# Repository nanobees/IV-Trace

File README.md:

# IV-Trace
DIY Four Probe IV Characterization for Graphene Studies

Eagle and LabView files for DIY four probe mesaurement device for graphene hall effect devices and transistor.

The files in this repository are for graphene device characterization project for Advanced Project Laboratory course that held 
in  Physics Department of Istanbul Technical University, Istanbul with the facilities of Nanoscale Surface Science Laboratory
with the Supervisor of Prof. Oguzhan Gurlu. The project is suported by Tubitak 1003 project with the grant number of 114F036.

In this project an Arduino is used for measuring currents and a Tektronix made oscillator is for reading voltage across a four probe graphene device. The voltage is supplied via Keithley 2400 sourcemeter. The Sourcemeter is controlled via LabView with specific instrument drivers. Oscilloscope and Arduino Data read via Labview with specific instrument driver for 
oscilloscope and LINX drivers for Arduino. In Labview the Current-Voltage graphs plotted for four separate probes.

In order to read the current flowing through the sample and I/V converter is made with precise shunt resistors. After that
the voltage converted flows through a very precise instrumentation amplifier; Analog Devices AD629 amplifier. The signal than
goes through Arduino and via serial port read with LabView.

For further information you can contact with me; haltugyildirim_at_protonmail.com

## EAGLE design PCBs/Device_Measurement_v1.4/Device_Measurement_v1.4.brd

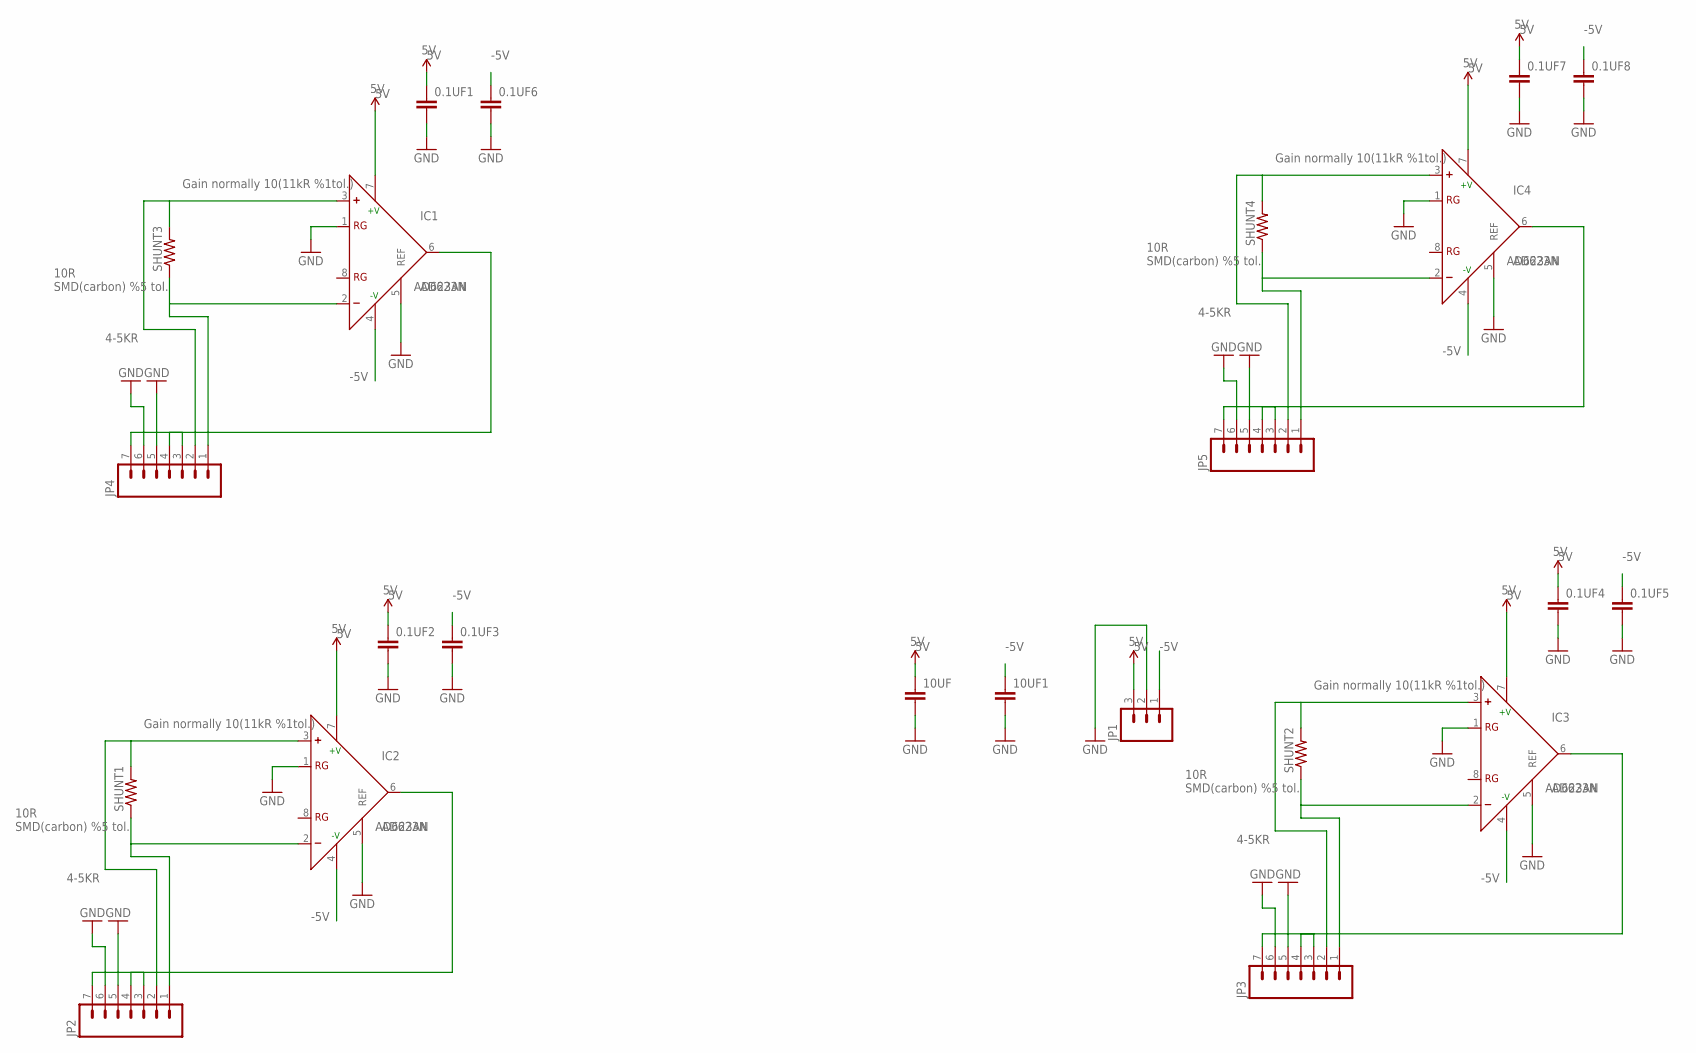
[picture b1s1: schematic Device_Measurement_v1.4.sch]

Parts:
0.1UF1, 0.1UF2, 0.1UF3, 0.1UF4, 0.1UF5, 0.1UF6, 0.1UF7, 0.1UF8, 10UF, 10UF1: CAPPTH1; CAP-PTH-5MM
IC1, IC2, IC3, IC4: AD623N; DIL08
JP1: M03LOCK; 1X03_LOCK
JP2, JP3, JP4, JP5: M07; 1X07
SHUNT1, SHUNT2, SHUNT3, SHUNT4: RESISTOR1206; 1206

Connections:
5V: 0.1UF1.1, 0.1UF2.1, 0.1UF4.1, 0.1UF7.1, 10UF.1, IC1.7 (+V), IC2.7 (+V), IC3.7 (+V), IC4.7 (+V), JP1.3
-5V: 0.1UF3.1, 0.1UF5.1, 0.1UF6.1, 0.1UF8.1, 10UF1.1, IC1.4 (-V), IC2.4 (-V), IC3.4 (-V), IC4.4 (-V), JP1.1
GND: 0.1UF1.2, 0.1UF2.2, 0.1UF3.2, 0.1UF4.2, 0.1UF5.2, 0.1UF6.2, 0.1UF7.2, 0.1UF8.2, 10UF.2, 10UF1.2, IC1.1 (RG), IC1.5 (REF), IC2.1 (RG), IC2.5 (REF), IC3.1 (RG), IC3.5 (REF), IC4.1 (RG), IC4.5 (REF), JP1.2, JP2.5, JP2.6, JP3.5, JP3.6, JP4.5, JP4.6, JP5.5, JP5.6
unnamed: IC2.3 (+), JP2.2, SHUNT1.2
unnamed: IC2.2 (-), JP2.1, SHUNT1.1
unnamed: IC1.3 (+), JP4.2, SHUNT3.2
unnamed: IC1.2 (-), JP4.1, SHUNT3.1
unnamed: IC1.6 (OUT), JP4.7
unnamed: JP4.3, JP4.4
unnamed: IC3.3 (+), JP3.2, SHUNT2.2
unnamed: IC2.6 (OUT), JP2.7
unnamed: JP2.3, JP2.4
unnamed: IC3.2 (-), JP3.1, SHUNT2.1
unnamed: IC3.6 (OUT), JP3.7
unnamed: JP3.3, JP3.4
unnamed: IC4.3 (+), JP5.2, SHUNT4.2
unnamed: IC4.2 (-), JP5.1, SHUNT4.1
unnamed: IC4.6 (OUT), JP5.7
unnamed: JP5.3, JP5.4

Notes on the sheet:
10R SMD(carbon) %5 tol.
Gain normally 10(11kR %1tol.)
4-5KR
AD623AN

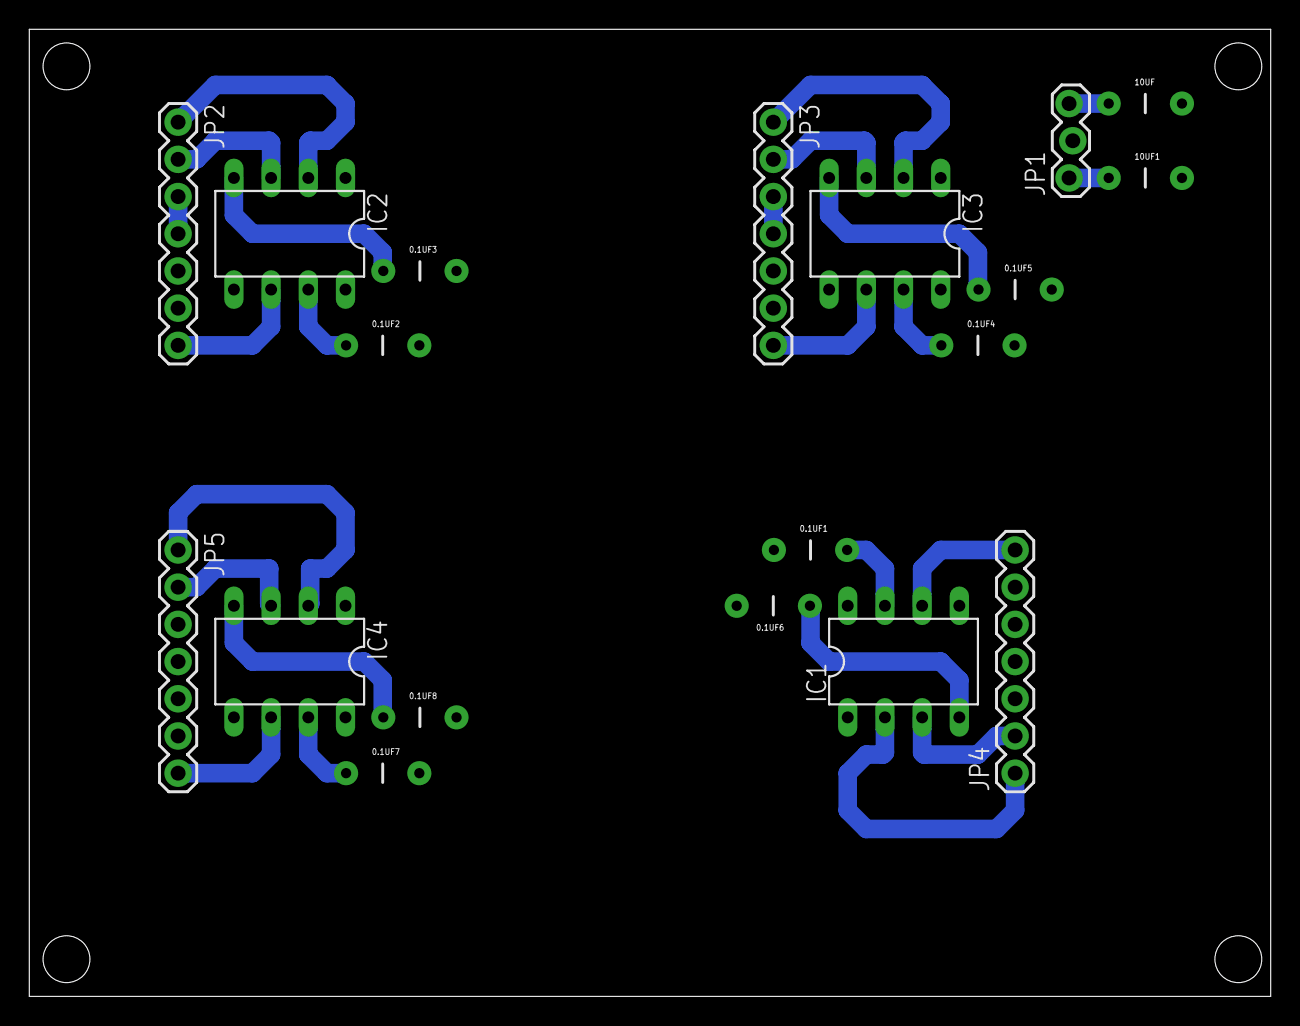
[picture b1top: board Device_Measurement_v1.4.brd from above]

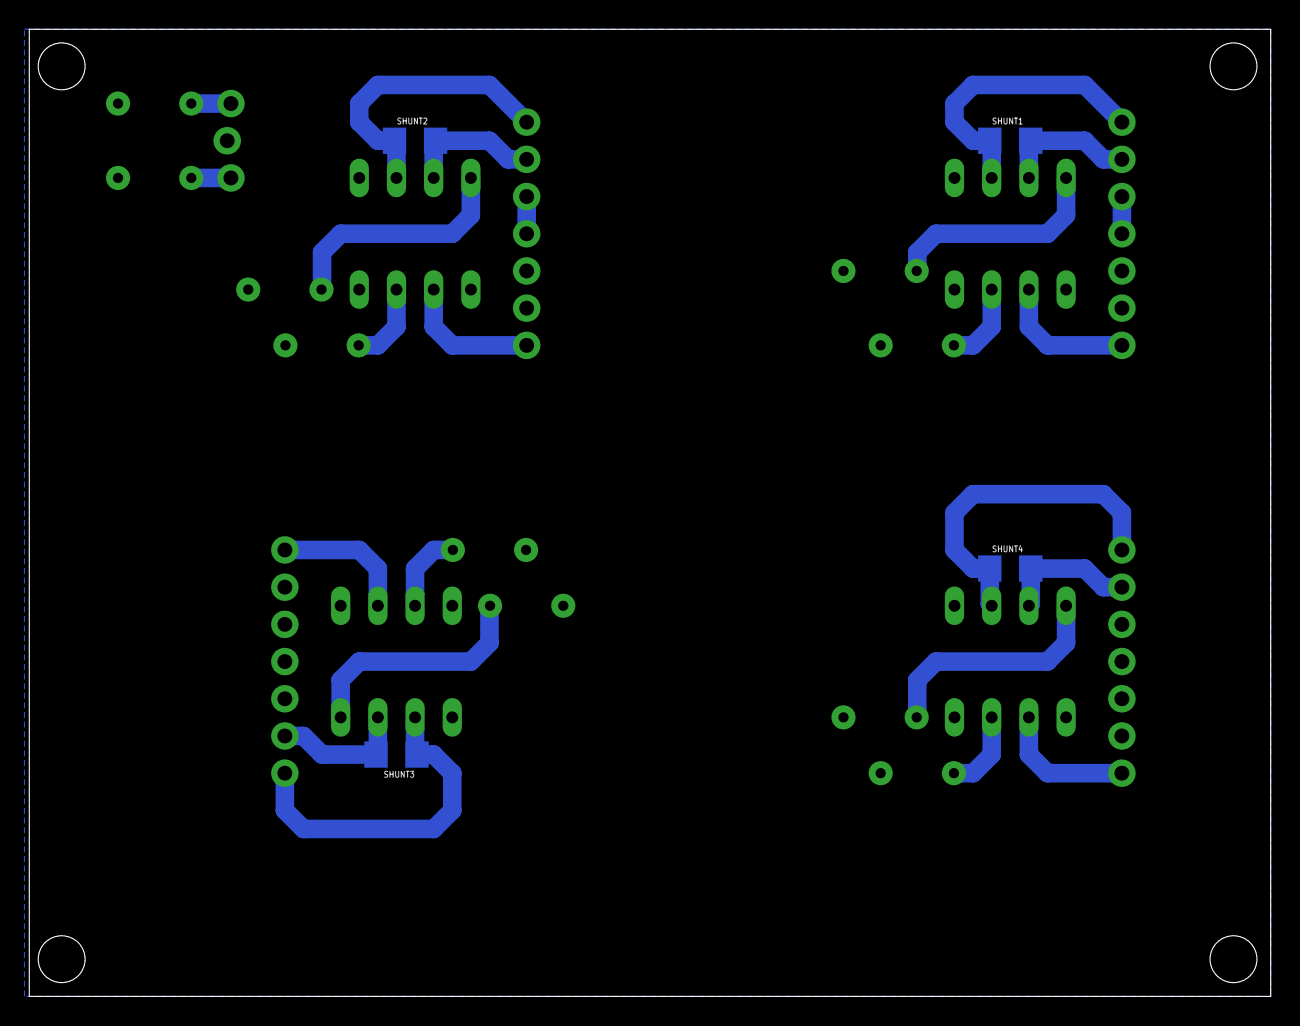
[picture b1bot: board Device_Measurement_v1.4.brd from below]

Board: 2 copper layers, 84.8 x 66.0 mm, 23 parts (4 on the bottom side), 19 nets.

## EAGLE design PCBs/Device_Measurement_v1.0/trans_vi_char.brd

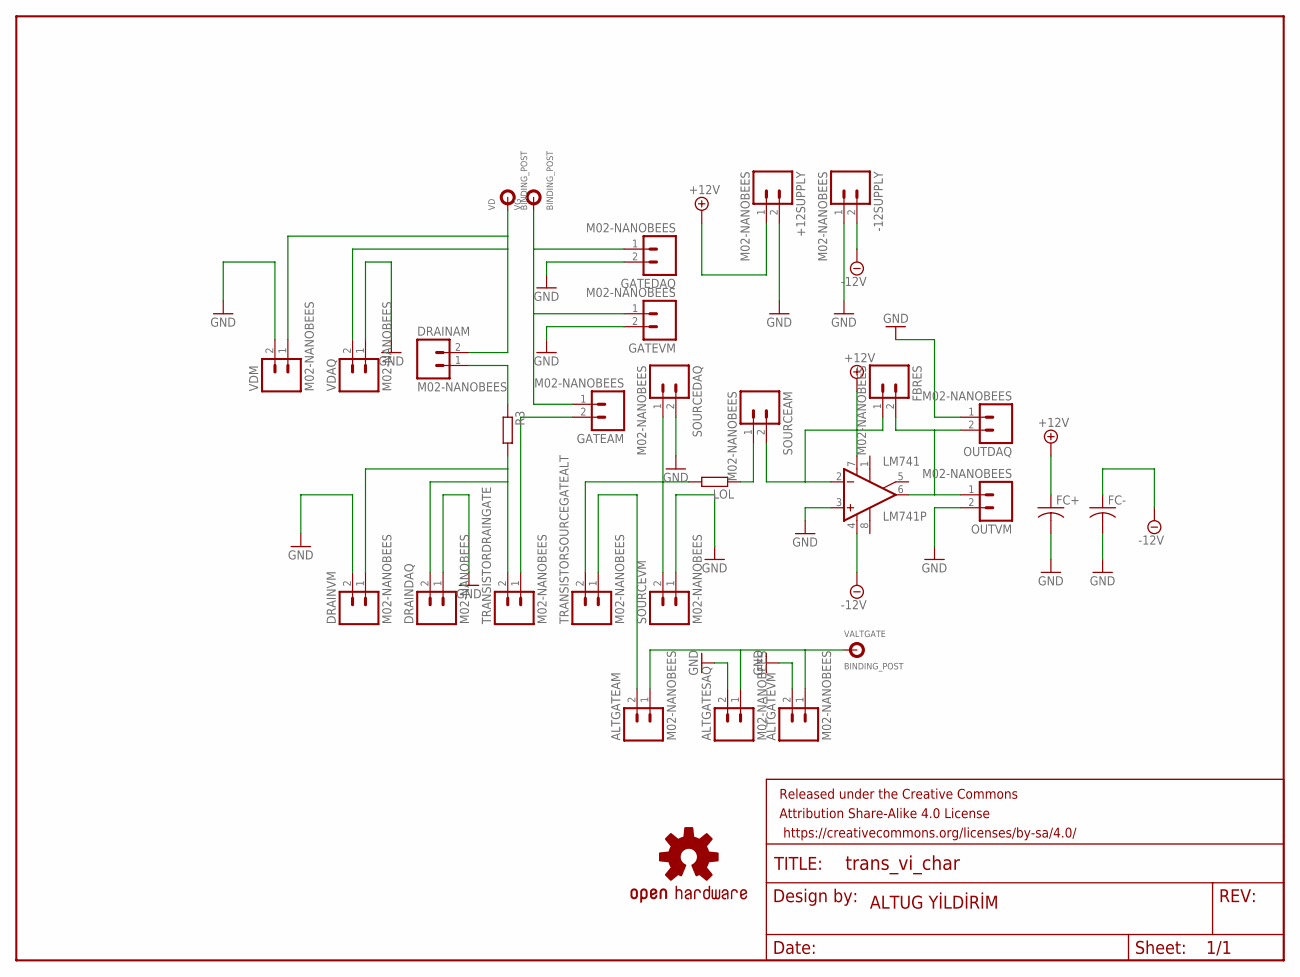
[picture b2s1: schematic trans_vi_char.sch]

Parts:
+12SUPPLY: M02-NANOBEES
-12SUPPLY: M02-NANOBEES
ALTGATEAM: M02-NANOBEES
ALTGATESAQ: M02-NANOBEES
ALTGATEVM: M02-NANOBEES
DRAINAM: M02-NANOBEES
DRAINDAQ: M02-NANOBEES
DRAINVM: M02-NANOBEES
FBRES: M02-NANOBEES
FC+: C-US025-025X050; C025-025X050
FC-: C-US025-025X050; C025-025X050
FRAME1: FRAME-LETTER; CREATIVE_COMMONS
GATEAM: M02-NANOBEES
GATEDAQ: M02-NANOBEES
GATEVM: M02-NANOBEES
LM741: LM741P; DIL08
LOGO1: OSHW-LOGOM; OSHW-LOGO-M
LOL: R-EU_0204/7; 0204/7
OUTDAQ: M02-NANOBEES
OUTVM: M02-NANOBEES
R3: R-EU_0204/7; 0204/7
SOURCEAM: M02-NANOBEES
SOURCEDAQ: M02-NANOBEES
SOURCEVM: M02-NANOBEES
TRANSISTORDRAINGATE: M02-NANOBEES
TRANSISTORSOURCEGATEALT: M02-NANOBEES
VALTGATE: BINDING_POST
VD: BINDING_POST
VDAQ: M02-NANOBEES
VDM: M02-NANOBEES
VG: BINDING_POST

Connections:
+12V: +12SUPPLY.1, FC+.1, LM741.7 (V+)
-12V: -12SUPPLY.2, FC-.1, LM741.4 (V-)
GND: +12SUPPLY.2, -12SUPPLY.1, ALTGATESAQ.2, ALTGATEVM.2, DRAINDAQ.1, DRAINVM.2, FC+.2, FC-.2, GATEDAQ.2, GATEVM.2, LM741.3 (-IN), OUTDAQ.1, OUTVM.2, SOURCEDAQ.2, SOURCEVM.1, VDAQ.1, VDM.2
unnamed: FBRES.2, LM741.6 (OUT), OUTDAQ.2, OUTVM.1
unnamed: FBRES.1, LM741.2 (+IN), SOURCEAM.2
unnamed: DRAINDAQ.2, DRAINVM.1, R3.2, TRANSISTORDRAINGATE.2
unnamed: LOL.2, SOURCEDAQ.1, SOURCEVM.2, TRANSISTORSOURCEGATEALT.2
unnamed: DRAINAM.1, R3.1
unnamed: ALTGATEAM.2, TRANSISTORSOURCEGATEALT.1
unnamed: GATEAM.2, TRANSISTORDRAINGATE.1
unnamed: GATEAM.1, GATEDAQ.1, GATEVM.1, VG.P$1
unnamed: DRAINAM.2, VD.P$1, VDAQ.2, VDM.1
unnamed: ALTGATEAM.1, ALTGATESAQ.1, ALTGATEVM.1, VALTGATE.P$1
unnamed: LOL.1, SOURCEAM.1

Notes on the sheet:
ALTUG YİLDİRİM

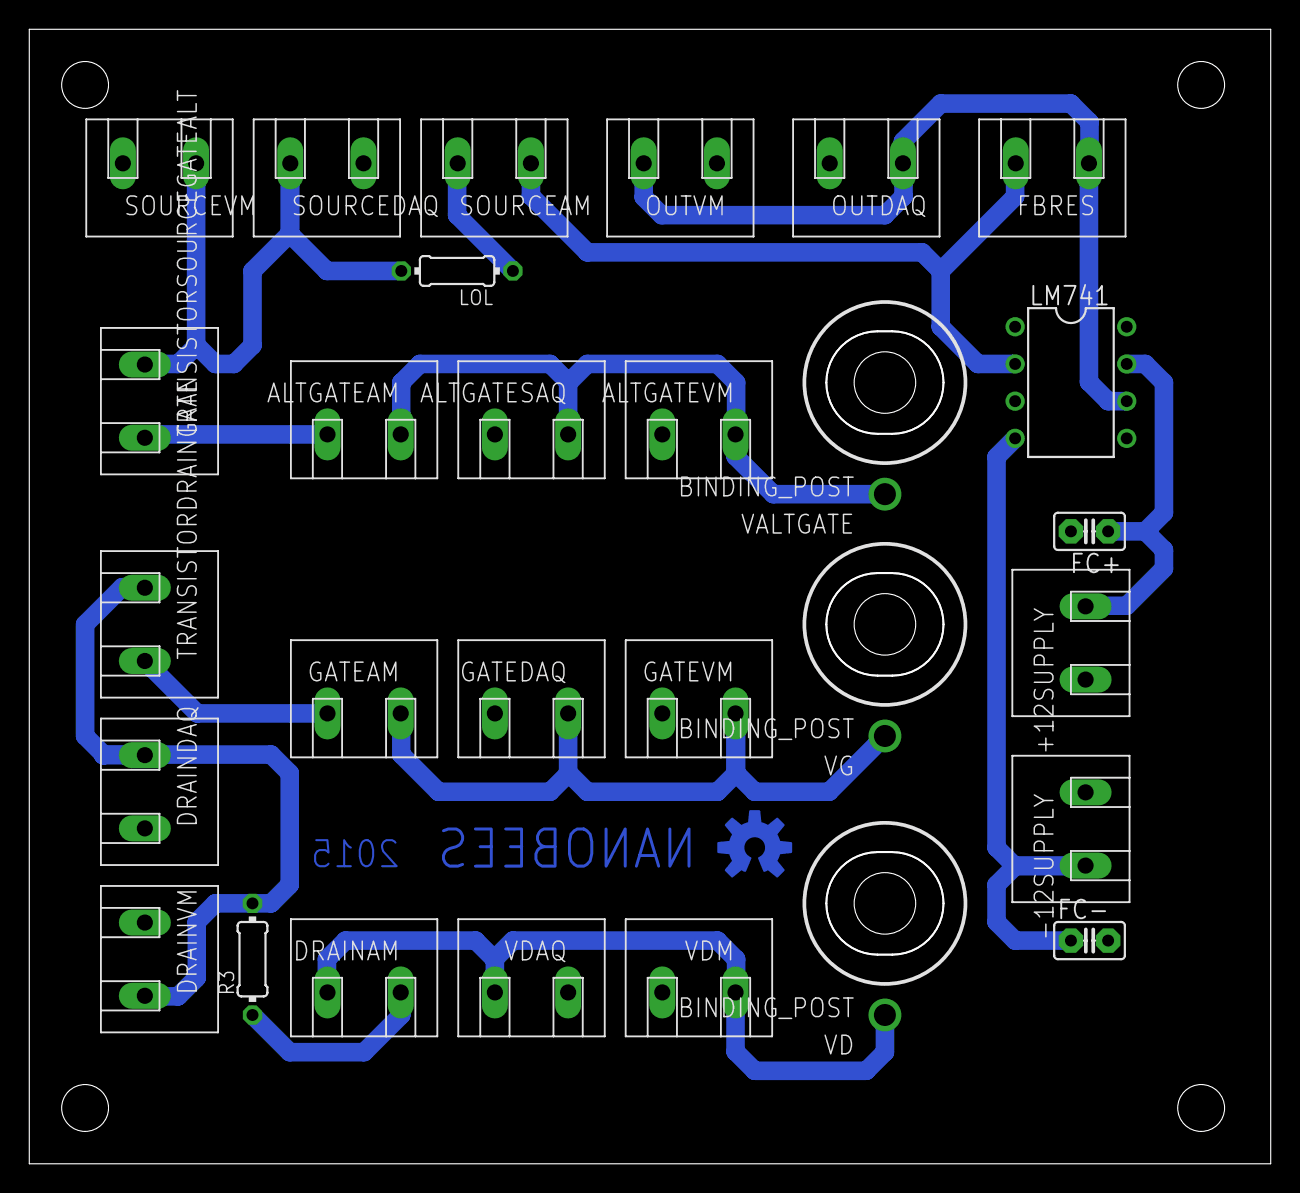
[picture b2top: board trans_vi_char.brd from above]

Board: 2 copper layers, 84.6 x 77.3 mm, 31 parts (0 on the bottom side), 14 nets.

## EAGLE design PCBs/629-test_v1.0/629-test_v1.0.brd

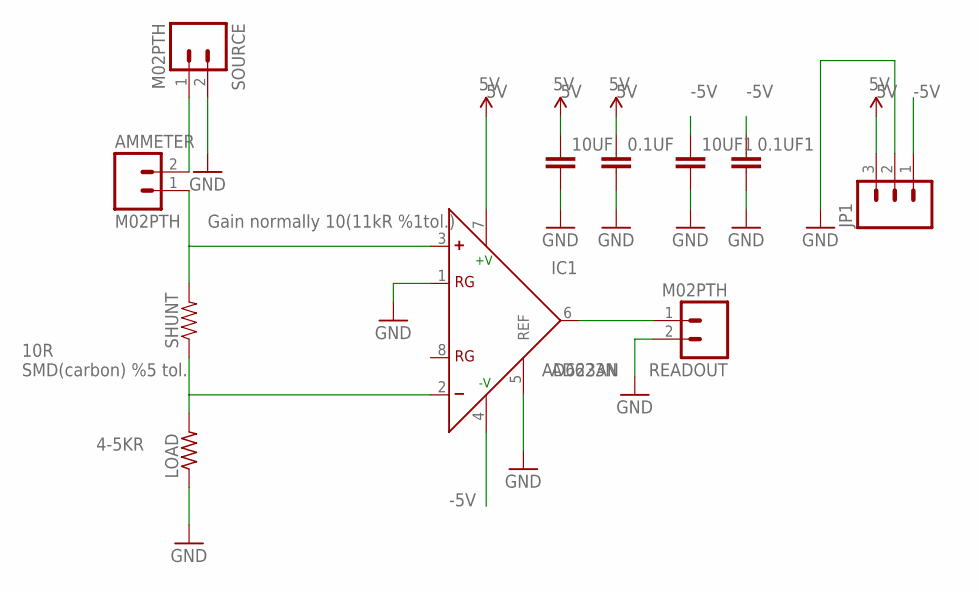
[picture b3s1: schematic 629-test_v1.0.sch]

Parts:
0.1UF, 0.1UF1, 10UF, 10UF1: CAPPTH1; CAP-PTH-5MM
AMMETER: M02PTH; 1X02
IC1: AD623N; DIL08
JP1: M03LOCK; 1X03_LOCK
LOAD: R-US_0207/10; 0207/10
READOUT: M02PTH; 1X02
SHUNT: RESISTOR1206; 1206
SOURCE: M02PTH; 1X02

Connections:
5V: 0.1UF.1, 10UF.1, IC1.7 (+V), JP1.3
-5V: 0.1UF1.1, 10UF1.1, IC1.4 (-V), JP1.1
GND: 0.1UF.2, 0.1UF1.2, 10UF.2, 10UF1.2, IC1.1 (RG), IC1.5 (REF), JP1.2, LOAD.1, READOUT.2, SOURCE.2
unnamed: AMMETER.1, IC1.3 (+), SHUNT.2
unnamed: IC1.2 (-), LOAD.2, SHUNT.1
unnamed: AMMETER.2, SOURCE.1
unnamed: IC1.6 (OUT), READOUT.1

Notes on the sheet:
10R SMD(carbon) %5 tol.
Gain normally 10(11kR %1tol.)
4-5KR
AD623AN

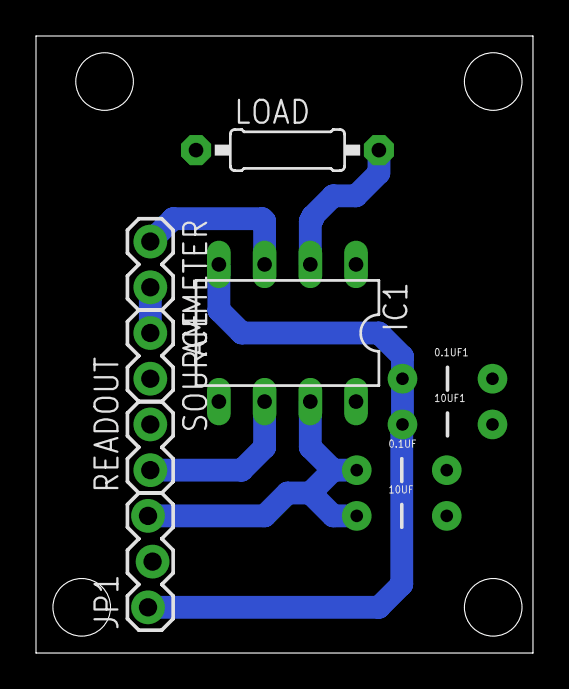
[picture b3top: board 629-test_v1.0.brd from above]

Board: 2 copper layers, 27.6 x 34.3 mm, 11 parts (1 on the bottom side), 7 nets.

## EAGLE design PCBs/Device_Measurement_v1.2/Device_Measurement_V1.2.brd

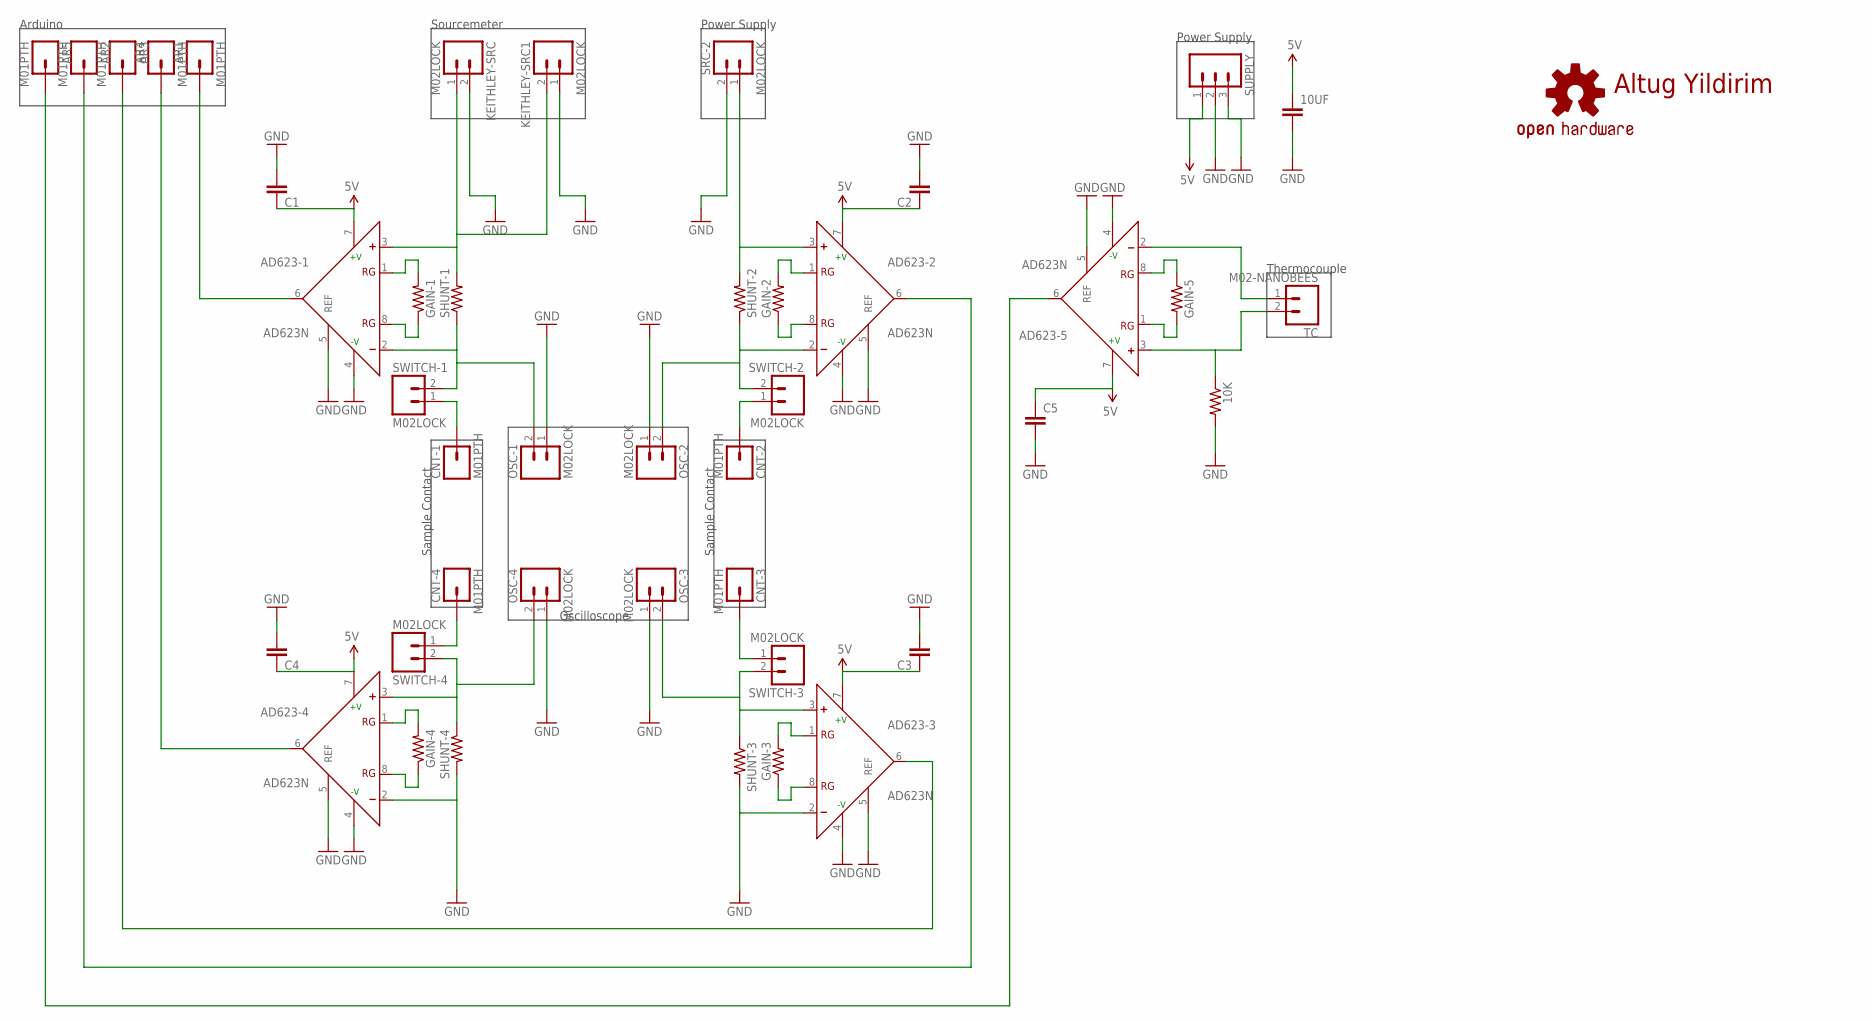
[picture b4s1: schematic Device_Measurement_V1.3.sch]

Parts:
10K: R-US_0207/10; 0207/10
10UF: CAPPTH1; CAP-PTH-5MM
AD623-1, AD623-2, AD623-3, AD623-4, AD623-5: AD623N; DIL08
AR1, AR2, AR3, AR4, AR5: M01PTH; 1X01
C1, C2, C3, C4, C5: CAPPTH1; CAP-PTH-5MM
CNT-1, CNT-2, CNT-3, CNT-4: M01PTH; 1X01
GAIN-1, GAIN-2, GAIN-3, GAIN-4, GAIN-5: R-US_0207/10; 0207/10
KEITHLEY-SRC, KEITHLEY-SRC1: M02LOCK; 1X02_LOCK
LOGO1: OSHW-LOGOM; OSHW-LOGO-M
OSC-1, OSC-2, OSC-3, OSC-4: M02LOCK; 1X02_LOCK
SHUNT-1, SHUNT-2, SHUNT-3, SHUNT-4: RESISTOR1206; 1206
SRC-2: M02LOCK; 1X02_LOCK
SUPPLY: M03PTH; 1X03
SWITCH-1, SWITCH-2, SWITCH-3, SWITCH-4: M02LOCK; 1X02_LOCK
TC: M02-NANOBEES

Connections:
5V: 10UF.1, AD623-1.7 (+V), AD623-2.7 (+V), AD623-3.7 (+V), AD623-4.7 (+V), AD623-5.7 (+V), C1.1, C2.1, C3.1, C4.1, C5.1, SUPPLY.1
GND: 10K.2, 10UF.2, AD623-1.4 (-V), AD623-1.5 (REF), AD623-2.4 (-V), AD623-2.5 (REF), AD623-3.2 (-), AD623-3.4 (-V), AD623-3.5 (REF), AD623-4.2 (-), AD623-4.4 (-V), AD623-4.5 (REF), AD623-5.4 (-V), AD623-5.5 (REF), C1.2, C2.2, C3.2, C4.2, C5.2, KEITHLEY-SRC.2, KEITHLEY-SRC1.1, OSC-1.1, OSC-2.1, OSC-3.1, OSC-4.1, SHUNT-3.2, SHUNT-4.2, SRC-2.2, SUPPLY.2, SUPPLY.3
unnamed: AD623-1.6 (OUT), AR1.1
unnamed: CNT-1.1, SWITCH-1.1
unnamed: AD623-2.6 (OUT), AR2.1
unnamed: AD623-1.1 (RG), GAIN-1.2
unnamed: AD623-4.6 (OUT), AR4.1
unnamed: AD623-1.8 (RG), GAIN-1.1
unnamed: AD623-3.6 (OUT), AR3.1
unnamed: AD623-2.2 (-), OSC-2.2, SHUNT-2.1, SWITCH-2.2
unnamed: AD623-5.6 (OUT), AR5.1
unnamed: AD623-4.3 (+), OSC-4.2, SHUNT-4.1, SWITCH-4.2
unnamed: AD623-2.3 (+), SHUNT-2.2, SRC-2.1
unnamed: CNT-2.1, SWITCH-2.1
unnamed: AD623-2.1 (RG), GAIN-2.2
unnamed: AD623-2.8 (RG), GAIN-2.1
unnamed: AD623-3.3 (+), OSC-3.2, SHUNT-3.1, SWITCH-3.2
unnamed: 10K.1, AD623-5.3 (+), TC.2
unnamed: CNT-4.1, SWITCH-4.1
unnamed: CNT-3.1, SWITCH-3.1
unnamed: AD623-3.1 (RG), GAIN-3.2
unnamed: AD623-3.8 (RG), GAIN-3.1
unnamed: AD623-4.1 (RG), GAIN-4.2
unnamed: AD623-4.8 (RG), GAIN-4.1
unnamed: AD623-5.2 (-), TC.1
unnamed: AD623-5.1 (RG), GAIN-5.2
unnamed: AD623-5.8 (RG), GAIN-5.1
unnamed: AD623-1.2 (-), OSC-1.2, SHUNT-1.1, SWITCH-1.2
unnamed: AD623-1.3 (+), KEITHLEY-SRC.1, KEITHLEY-SRC1.2, SHUNT-1.2

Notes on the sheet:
Altug Yildirim
Oscilloscope
Sample Contact
Sourcemeter
Power Supply
Arduino
Thermocouple

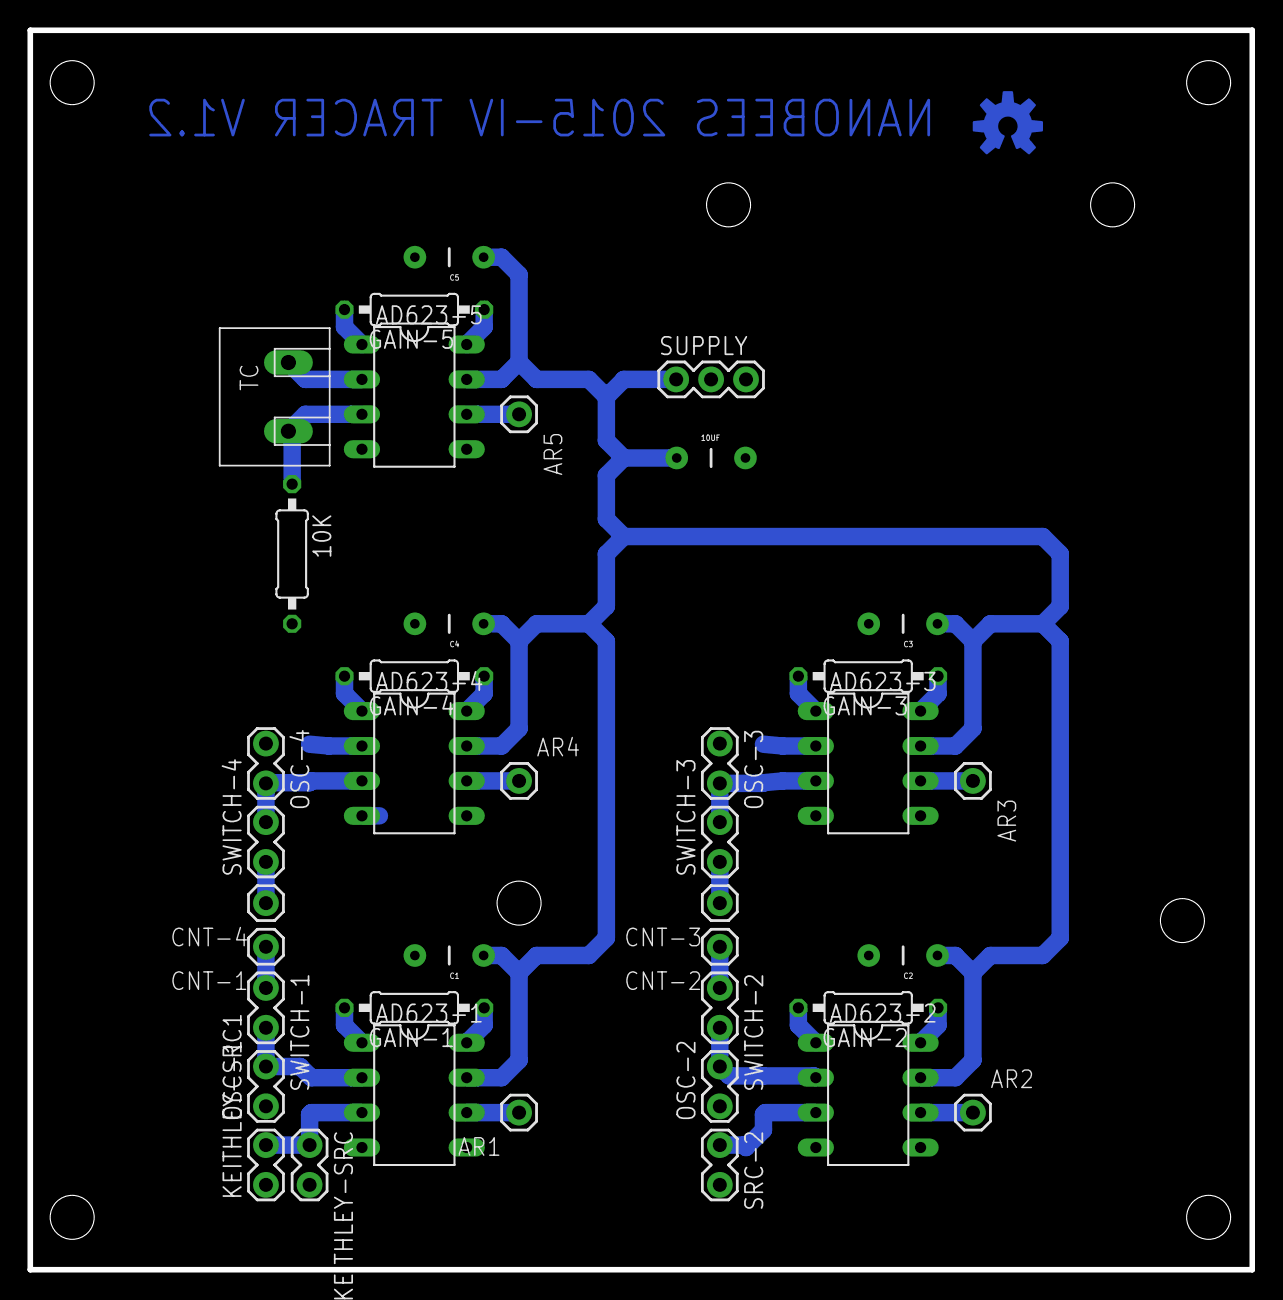
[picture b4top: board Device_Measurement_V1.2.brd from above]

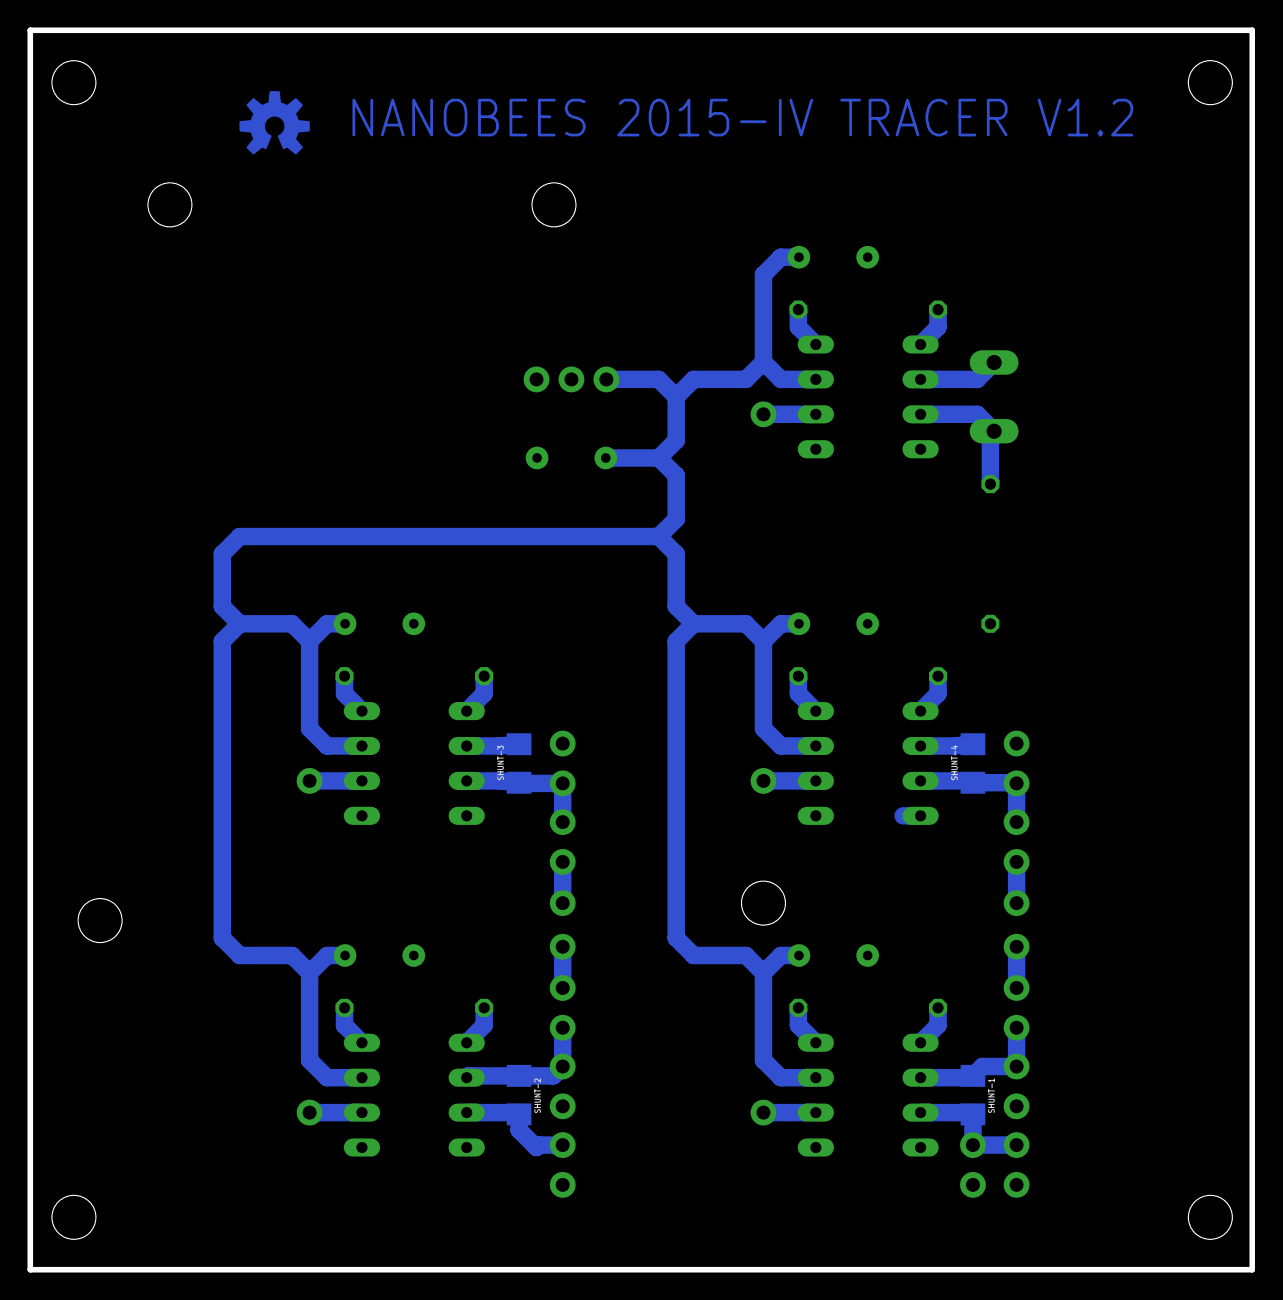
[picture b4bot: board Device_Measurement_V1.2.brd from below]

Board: 2 copper layers, 88.9 x 90.2 mm, 44 parts (4 on the bottom side), 29 nets.

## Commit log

2016-08-26 :lollipop: Added .gitattributes & .gitignore files
2016-08-26 initial codes and CB files
    adding files
2016-08-28 adding further versions of PCB files and a general image of the system
    adding files
2017-08-08 new four probe

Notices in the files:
parts and their libraries:
SparkFun-Capacitors: Licensing: Creative Commons ShareAlike 4.0 International - https://creativecommons.org/licenses/by-sa/4.0
SparkFun-Aesthetics: Released under the Creative Commons Attribution Share-Alike 4.0 License
SparkFun-Aesthetics: https://creativecommons.org/licenses/by-sa/4.0
